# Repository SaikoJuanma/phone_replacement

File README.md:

this projects aims to create a replacement for the phone, so I can stop using my phone on the home and get rid off distractions.
## Upcoming features
1. Timer and alarm.
2. PCB and schematics for the project.
3. 3D desings for the project.
4. Habit tracker.

When the project makes progress help will be included on how to set it up, how to print, etc.
New features will be revised when all the previous ones are met.

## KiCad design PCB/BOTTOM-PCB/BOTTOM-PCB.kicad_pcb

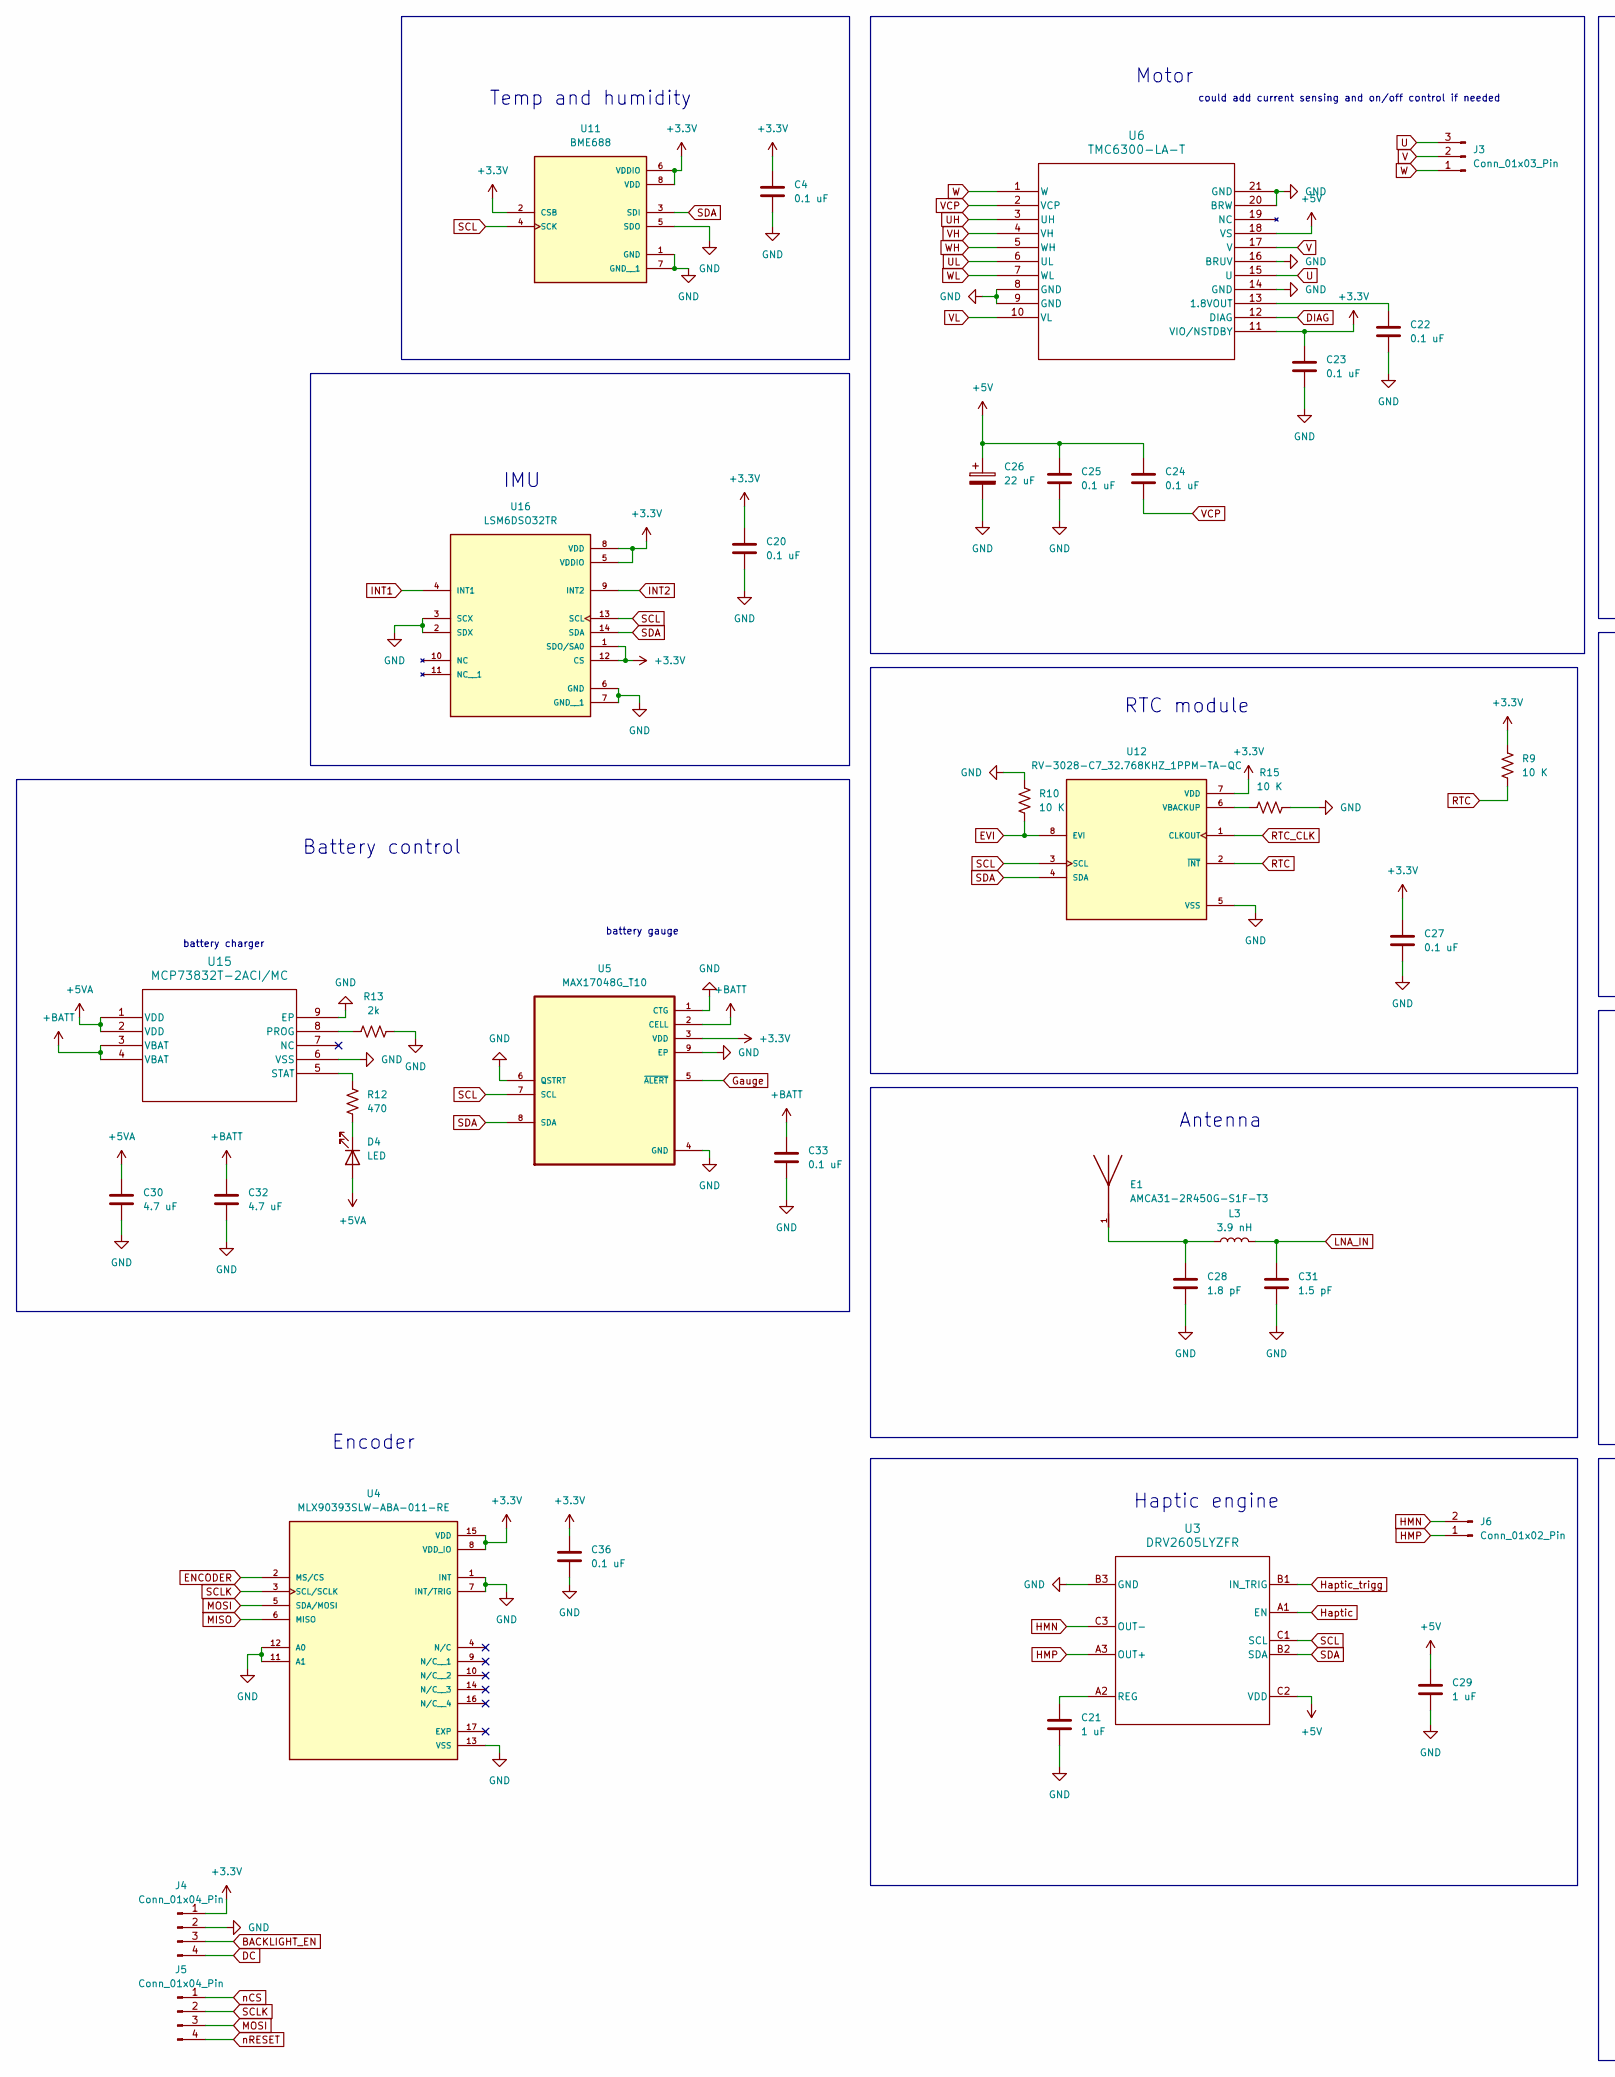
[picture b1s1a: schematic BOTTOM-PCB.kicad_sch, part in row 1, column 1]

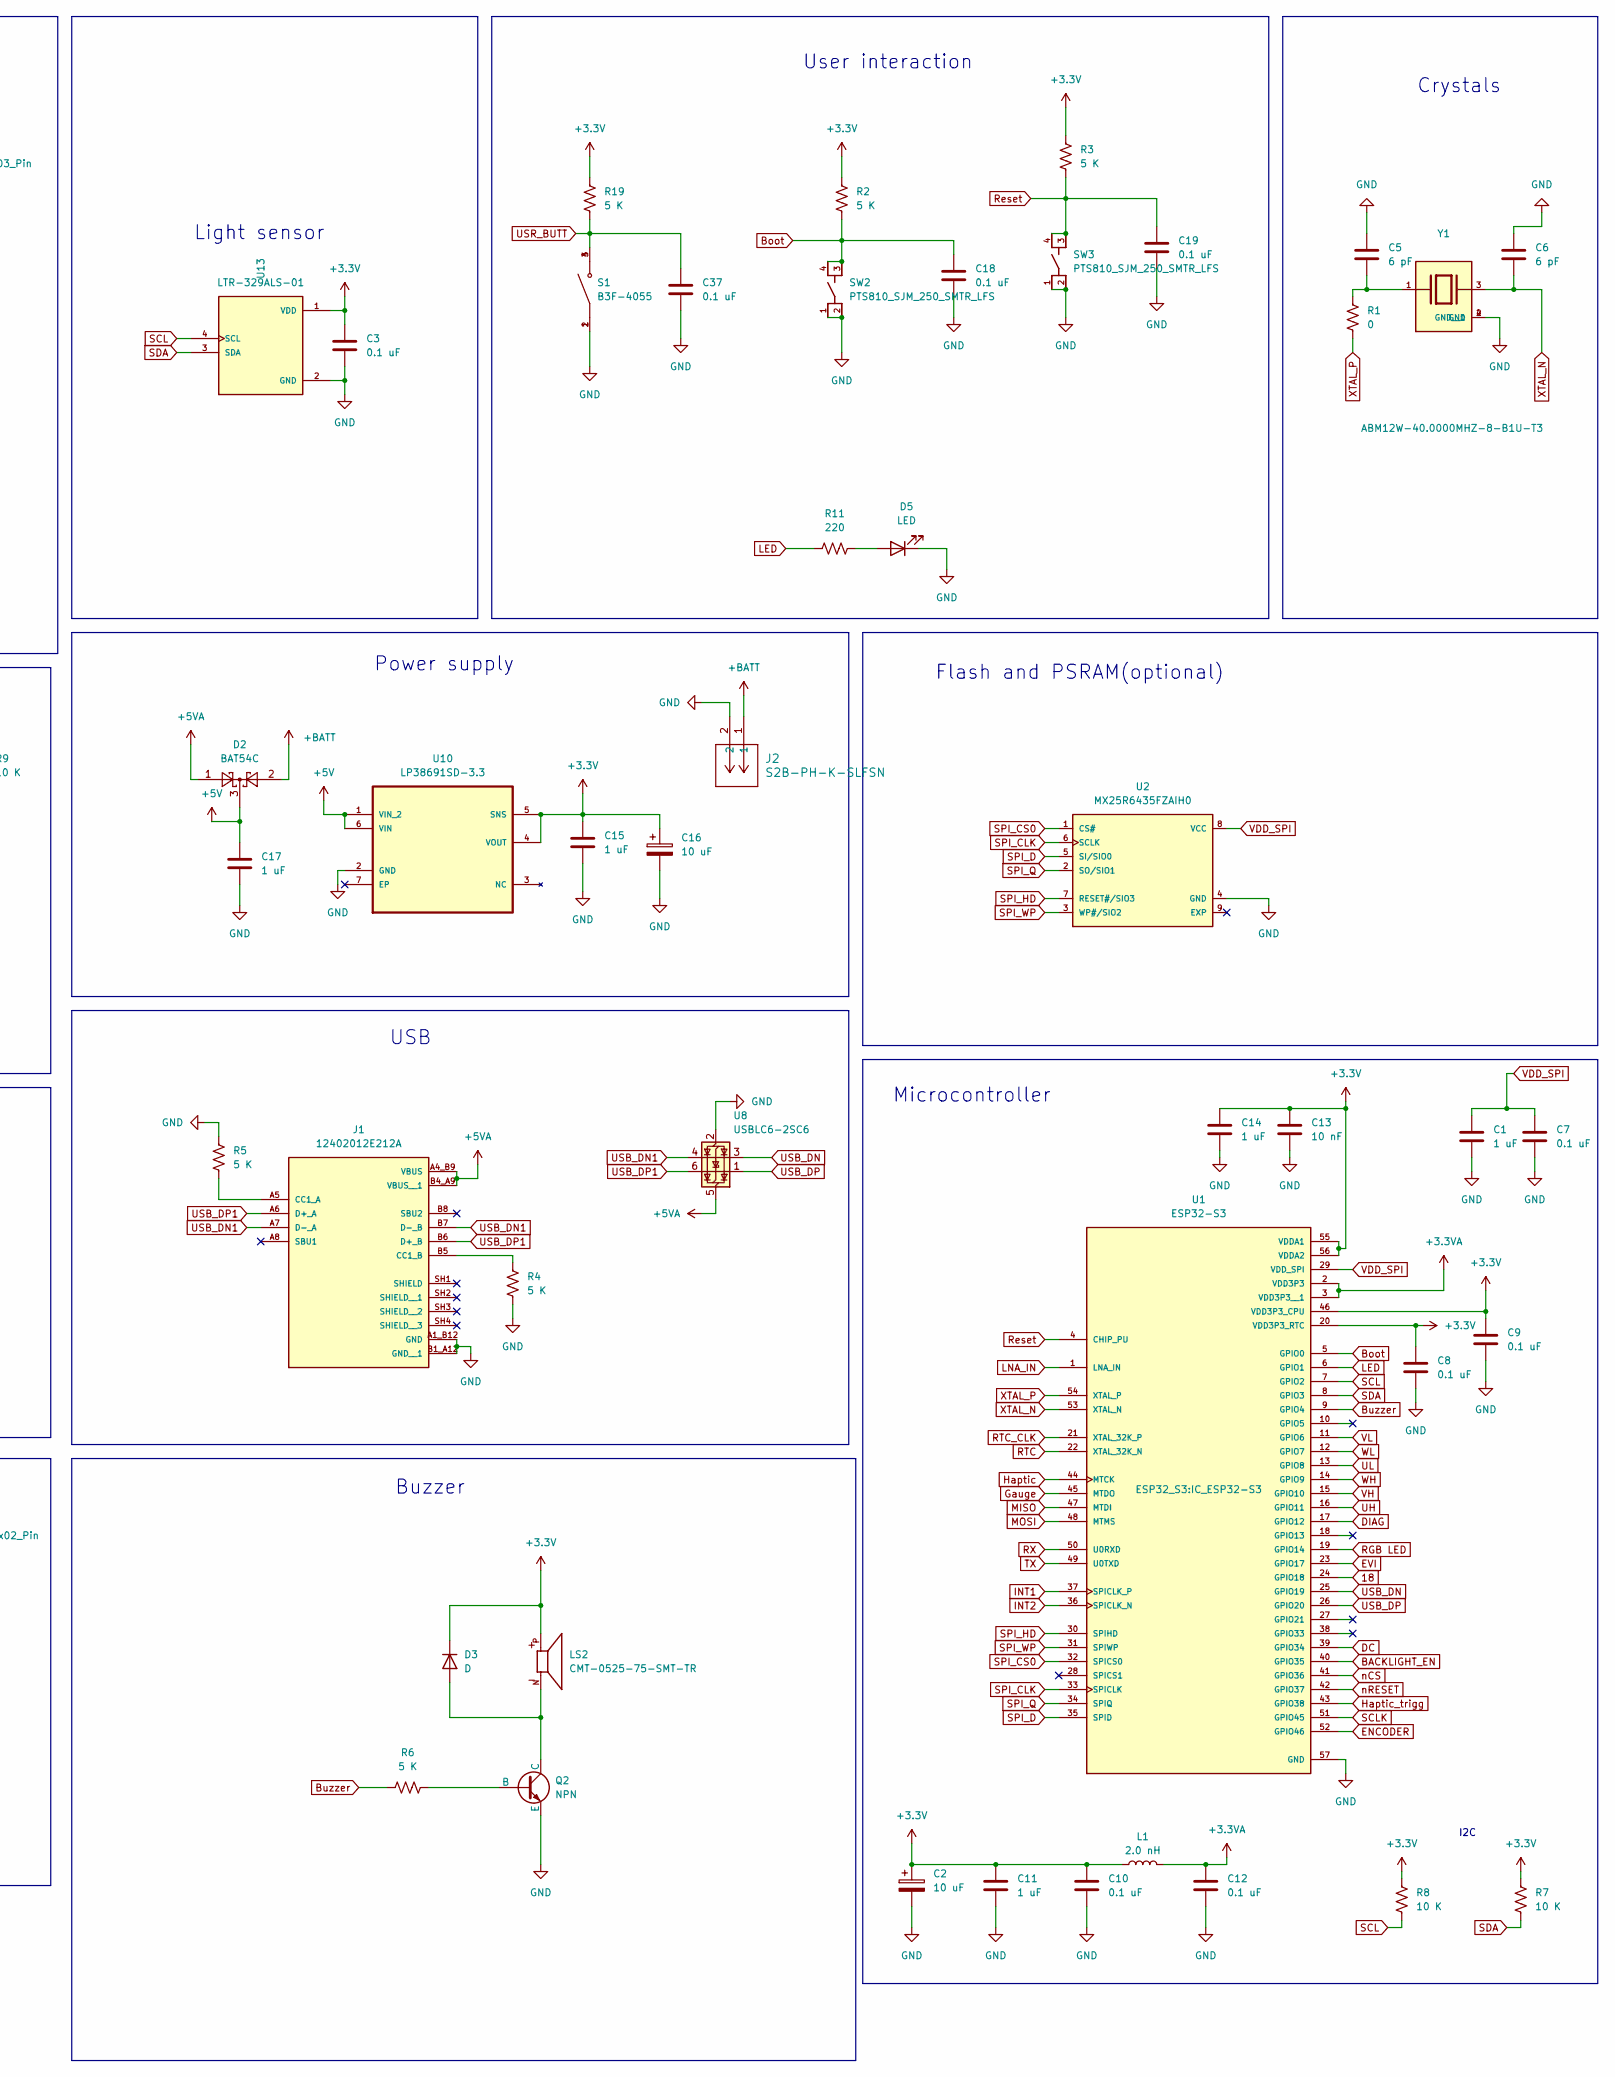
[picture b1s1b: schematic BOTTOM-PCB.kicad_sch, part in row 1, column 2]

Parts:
C1, C11, C14, C15, C17, C21, C29: 1 uF; C_0402_1005Metric_Pad0.74x0.62mm_HandSolder
C2, C16: 10 uF; CP_EIA-1608-08_AVX-J_HandSolder
C3, C4, C7, C8, C9, C10, C12, C18, C19, C20, C22, C23, C24, C25, C27, C33, C36, C37: 0.1 uF; C_0402_1005Metric_Pad0.74x0.62mm_HandSolder
C5, C6: 6 pF; C_0402_1005Metric_Pad0.74x0.62mm_HandSolder
C13: 10 nF; C_0402_1005Metric_Pad0.74x0.62mm_HandSolder
C26: 22 uF; CP_EIA-1608-08_AVX-J_HandSolder
C28: 1.8 pF; C_0201_0603Metric_Pad0.64x0.40mm_HandSolder
C30, C32: 4.7 uF; C_0402_1005Metric_Pad0.74x0.62mm_HandSolder
C31: 1.5 pF; C_0201_0603Metric_Pad0.64x0.40mm_HandSolder
D2: BAT54C; SOT-23
D3: D; D_0402_1005Metric_Pad0.77x0.64mm_HandSolder
D4, D5: LED; LED_0805_2012Metric
E1: AMCA31-2R450G-S1F-T3; XDCR_AMCA31-2R450G-S1F-T3; PARTREV 03-21-19
J1: 12402012E212A; AMPHENOL_12402012E212A; PARTREV 4
J2: S2B-PH-K-SLFSN; JST_ZH_B2B-ZR_1x02_P1.50mm_Vertical
J3: Conn_01x03_Pin; JST_ZH_B3B-ZR_1x03_P1.50mm_Vertical
J4, J5: Conn_01x04_Pin; PinHeader_1x04_P1.27mm_Vertical
J6: Conn_01x02_Pin; JST_ZH_B2B-ZR_1x02_P1.50mm_Vertical
L1: 2.0 nH; L_0402_1005Metric_Pad0.77x0.64mm_HandSolder
L3: 3.9 nH; L_0201_0603Metric_Pad0.64x0.40mm_HandSolder
LS2: CMT-0525-75-SMT-TR; XDCR_CMT-0525-75-SMT-TR; PARTREV 1.0
Q2: NPN; SOT-723
R1: 0; R_0402_1005Metric_Pad0.72x0.64mm_HandSolder
R2, R3, R4, R5, R6, R19: 5 K; R_0402_1005Metric_Pad0.72x0.64mm_HandSolder
R7, R8, R9, R10, R15: 10 K; R_0402_1005Metric_Pad0.72x0.64mm_HandSolder
R11: 220; R_0402_1005Metric_Pad0.72x0.64mm_HandSolder
R12: 470; R_0402_1005Metric_Pad0.72x0.64mm_HandSolder
R13: 2k; R_0402_1005Metric_Pad0.72x0.64mm_HandSolder
S1: B3F-4055; SW_B3F-4055; PARTREV A070-E1-08
SW2, SW3: PTS810_SJM_250_SMTR_LFS; SW_PTS810_SJM_250_SMTR_LFS
U1: ESP32-S3; IC_ESP32-S3; PARTREV v1.2
U2: MX25R6435FZAIH0; SON80P400X400X60-9N
U3: DRV2605LYZFR; YZF0009ADAD
U4: MLX90393SLW-ABA-011-RE; QFN50P300X300X100-17N; PARTREV 010
U5: MAX17048G_T10; SON50P200X200X80-9N
U6: TMC6300-LA-T; 21-100586_K2033&plus_1C_ADI-M; MPN 175-TMC6300-LA-TCT-ND
U8: USBLC6-2SC6; SOT-23-6
U10: LP38691SD-3.3; DFN300X300X80-7N; MPN LP38691SD-3.3
U11: BME688; IC_BME688; PARTREV 1.0
U12: RV-3028-C7_32.768KHZ_1PPM-TA-QC; MicroCrystal_C7_SON-8_1.5x3.2mm_P0.9mm; PARTREV 1.3
U13: LTR-329ALS-01; IC_LTR-329ALS-01; PARTREV 1.8
U15: MCP73832T-2ACI/MC; DFN8_2x3MC_MCH-L
U16: LSM6DSO32TR; XDCR_LSM6DSO32TR; PARTREV 1
Y1: ABM12W-40.0000MHZ-8-B1U-T3; XTAL_ABM12W-40.0000MHZ-8-B1U-T3; PARTREV 10.05.2020

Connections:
18: U1.24 (GPIO18)
+3.3V: C2.1, C3.1, C4.1, C8.1, C9.1, C10.1, C11.1, C13.1, C14.1, C15.1, C16.1, C20.1, C23.1, C27.2, C36.2, D3.1 (K), J4.1, L1.1, LS2.P, R2.1, R3.1, R7.2, R8.2, R9.2, R19.1, U1.20 (VDD3P3_RTC), U1.46 (VDD3P3_CPU), U1.55 (VDDA1), U1.56 (VDDA2), U4.8 (VDD_IO), U4.15 (VDD), U5.3 (VDD), U6.11 (VIO/NSTDBY), U10.4 (VOUT), U10.5 (SNS), U11.2 (CSB), U11.6 (VDDIO), U11.8 (VDD), U12.7 (VDD), U13.1 (VDD), U16.1 (SDO/SA0), U16.5 (VDDIO), U16.8 (VDD), U16.12 (CS)
+3.3VA: C12.1, L1.2, U1.2 (VDD3P3), U1.3 (VDD3P3__1)
+5V: C17.1, C24.1, C25.1, C26.1, C29.2, D2.3, U3.C2 (VDD), U6.18 (VS), U10.1 (VIN_2), U10.6 (VIN)
+5VA: C30.2, D2.1, D4.2 (A), J1.A4_B9 (VBUS), J1.B4_A9 (VBUS__1), U8.5 (VBUS), U15.1 (VDD), U15.2 (VDD)
+BATT: C32.2, C33.2, D2.2, J2.1, U5.2 (CELL), U15.3 (VBAT), U15.4 (VBAT)
BACKLIGHT_EN: J4.3, U1.40 (GPIO35)
Boot: C18.1, R2.2, SW2.3, SW2.4, U1.5 (GPIO0)
Buzzer: R6.2, U1.9 (GPIO4)
DC: J4.4, U1.39 (GPIO34)
DIAG: U1.17 (GPIO12), U6.12 (DIAG)
ENCODER: U1.52 (GPIO46), U4.2 (MS/CS)
EVI: R10.2, U1.23 (GPIO17), U12.8 (EVI)
GND: C1.2, C2.2, C3.2, C4.2, C5.1, C6.1, C7.2, C8.2, C9.2, C10.2, C11.2, C12.2, C13.2, C14.2, C15.2, C16.2, C17.2, C18.2, C19.2, C20.2, C21.1, C22.2, C23.2, C25.2, C26.2, C27.1, C28.1, C29.1, C30.1, C31.1, C32.1, C33.1, C36.1, C37.2, D5.1 (K), J1.A1_B12 (GND), J1.B1_A12 (GND__1), J2.2, J4.2, Q2.3 (E), R4.2, R5.1, R10.1, R13.2, R15.2, S1.1, S1.2, SW2.1, SW2.2, SW3.1, SW3.2, U1.57 (GND), U2.4 (GND), U3.B3 (GND), U4.1 (INT), U4.7 (INT/TRIG), U4.11 (A1), U4.12 (A0), U4.13 (VSS), U5.1 (CTG), U5.4 (GND), U5.6 (QSTRT), U5.9 (EP), U6.8 (GND), U6.9 (GND), U6.14 (GND), U6.16 (BRUV), U6.20 (BRW), U6.21 (GND), U8.2 (GND), U10.2 (GND), U11.1 (GND), U11.5 (SDO), U11.7 (GND__1), U12.5 (VSS), U13.2 (GND), U15.6 (VSS), U15.9 (EP), U16.2 (SDX), U16.3 (SCX), U16.6 (GND), U16.7 (GND__1), Y1.2 (GND), Y1.4 (GND__1)
Gauge: U1.45 (MTDO), U5.5 (~ALERT)
HMN: J6.2, U3.C3 (OUT-)
HMP: J6.1, U3.A3 (OUT+)
Haptic: U1.44 (MTCK), U3.A1 (EN)
Haptic_trigg: U1.43 (GPIO38), U3.B1 (IN_TRIG)
INT1: U1.37 (SPICLK_P), U16.4 (INT1)
INT2: U1.36 (SPICLK_N), U16.9 (INT2)
LED: R11.1, U1.6 (GPIO1)
LNA_IN: C31.2, L3.2, U1.1 (LNA_IN)
MISO: U1.47 (MTDI), U4.6 (MISO)
MOSI: J5.3, U1.48 (MTMS), U4.5 (SDA/MOSI)
unnamed: C5.2, R1.1, Y1.1
unnamed: C28.2, E1.1, L3.1
unnamed: D3.2 (A), LS2.N, Q2.1 (C)
unnamed: D4.1 (K), R12.2
unnamed: D5.2 (A), R11.2
unnamed: J1.A5 (CC1_A), R5.2
unnamed: J1.B5 (CC1_B), R4.1
unnamed: Q2.2 (B), R6.1
unnamed: C21.2, U3.A2 (REG)
unnamed: C22.1, U6.13 (1.8VOUT)
unnamed: R15.1, U12.6 (VBACKUP)
unnamed: R13.1, U15.8 (PROG)
unnamed: R12.1, U15.5 (STAT)
RGB LED: U1.19 (GPIO14)
RTC: R9.1, U1.22 (XTAL_32K_N), U12.2 (~INT)
RTC_CLK: U1.21 (XTAL_32K_P), U12.1 (CLKOUT)
RX: U1.50 (U0RXD)
Reset: C19.1, R3.2, SW3.3, SW3.4, U1.4 (CHIP_PU)
SCL: R8.1, U1.7 (GPIO2), U3.C1 (SCL), U5.7 (SCL), U11.4 (SCK), U12.3 (SCL), U13.4 (SCL), U16.13 (SCL)
SCLK: J5.2, U1.51 (GPIO45), U4.3 (SCL/SCLK)
SDA: R7.1, U1.8 (GPIO3), U3.B2 (SDA), U5.8 (SDA), U11.3 (SDI), U12.4 (SDA), U13.3 (SDA), U16.14 (SDA)
SPI_CLK: U1.33 (SPICLK), U2.6 (SCLK)
SPI_CS0: U1.32 (SPICS0), U2.1 (CS#)
SPI_D: U1.35 (SPID), U2.5 (SI/SIO0)
SPI_HD: U1.30 (SPIHD), U2.7 (RESET#/SIO3)
SPI_Q: U1.34 (SPIQ), U2.2 (SO/SIO1)
SPI_WP: U1.31 (SPIWP), U2.3 (WP#/SIO2)
TX: U1.49 (U0TXD)
U: J3.3, U6.15 (U)
UH: U1.16 (GPIO11), U6.3 (UH)
UL: U1.13 (GPIO8), U6.6 (UL)
USB_DN: U1.25 (GPIO19), U8.3 (I/O2)
USB_DN1: J1.A7 (D-_A), J1.B7 (D-_B), U8.4 (I/O2)
USB_DP: U1.26 (GPIO20), U8.1 (I/O1)
USB_DP1: J1.A6 (D+_A), J1.B6 (D+_B), U8.6 (I/O1)
USR_BUTT: C37.1, R19.2, S1.3, S1.4
V: J3.2, U6.17 (V)
VCP: C24.2, U6.2 (VCP)
VDD_SPI: C1.1, C7.1, U1.29 (VDD_SPI), U2.8 (VCC)
VH: U1.15 (GPIO10), U6.4 (VH)
VL: U1.11 (GPIO6), U6.10 (VL)
W: J3.1, U6.1 (W)
WH: U1.14 (GPIO9), U6.5 (WH)
WL: U1.12 (GPIO7), U6.7 (WL)
XTAL_N: C6.2, U1.53 (XTAL_N), Y1.3
XTAL_P: R1.2, U1.54 (XTAL_P)
nCS: J5.1, U1.41 (GPIO36)
nRESET: J5.4, U1.42 (GPIO37)

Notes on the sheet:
Antenna
Crystals
Motor
Flash and PSRAM(optional)
Encoder
could add current sensing and on/off control if needed
Microcontroller
Power supply
I2C
Temp and humidity
IMU
Haptic engine
Battery control
Light sensor
User interaction
battery gauge
battery charger
USB
RTC module
Buzzer

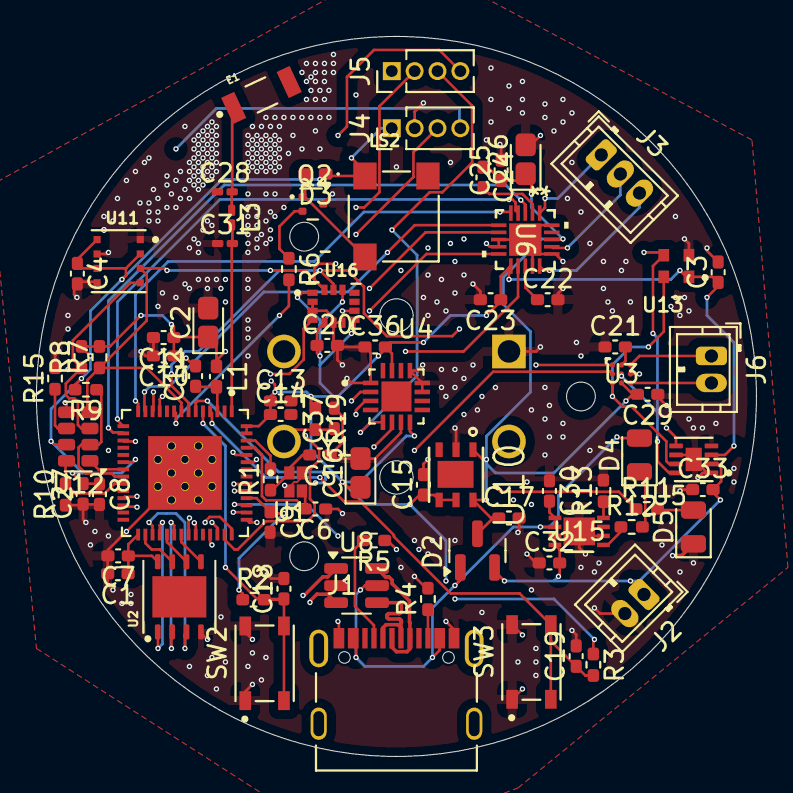
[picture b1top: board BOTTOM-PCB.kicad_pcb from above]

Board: 4 copper layers, 40.0 x 40.0 mm, 82 parts (1 on the bottom side), 69 nets.

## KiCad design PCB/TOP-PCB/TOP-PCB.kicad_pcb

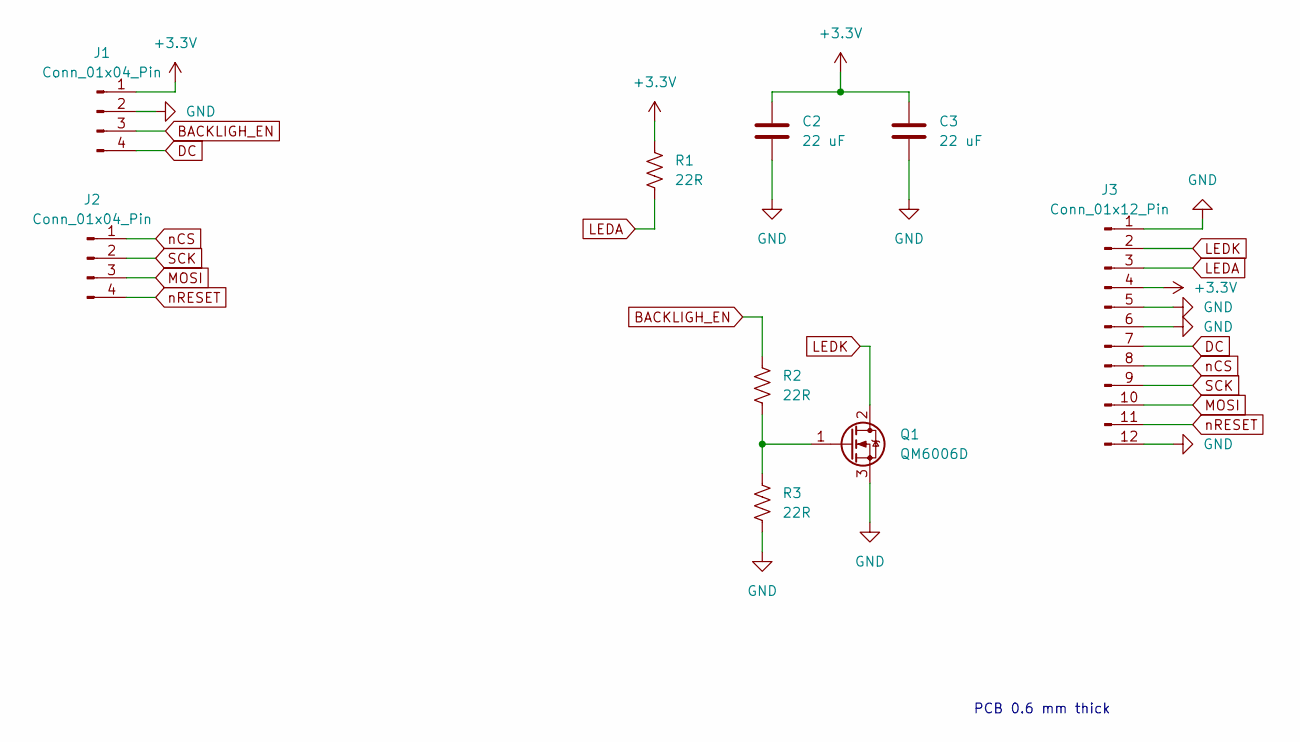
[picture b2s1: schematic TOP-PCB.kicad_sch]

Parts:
C2, C3: 22 uF; C_0201_0603Metric_Pad0.64x0.40mm_HandSolder
J1, J2: Conn_01x04_Pin; PinHeader_1x04_P1.27mm_Vertical
J3: Conn_01x12_Pin; GC9A01Round1.28
Q1: QM6006D; TO-252-2
R1, R2, R3: 22R; R_0201_0603Metric_Pad0.64x0.40mm_HandSolder

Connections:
+3.3V: C2.1, C3.1, J1.1, J3.4, R1.1
BACKLIGH_EN: J1.3, R2.1
DC: J1.4, J3.7
GND: C2.2, C3.2, J1.2, J3.1, J3.5, J3.6, J3.12, Q1.3 (S), R3.2
LEDA: J3.3, R1.2
LEDK: J3.2, Q1.2 (D)
MOSI: J2.3, J3.10
unnamed: Q1.1 (G), R2.2, R3.1
SCK: J2.2, J3.9
nCS: J2.1, J3.8
nRESET: J2.4, J3.11

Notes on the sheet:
PCB 0.6 mm thick

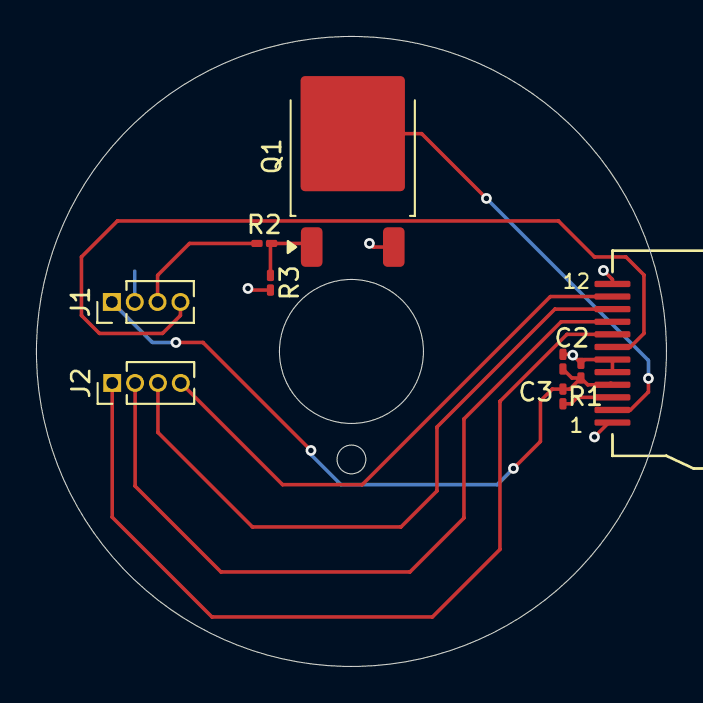
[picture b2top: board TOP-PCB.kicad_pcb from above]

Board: 2 copper layers, 35.0 x 35.0 mm, 9 parts (0 on the bottom side), 11 nets.
